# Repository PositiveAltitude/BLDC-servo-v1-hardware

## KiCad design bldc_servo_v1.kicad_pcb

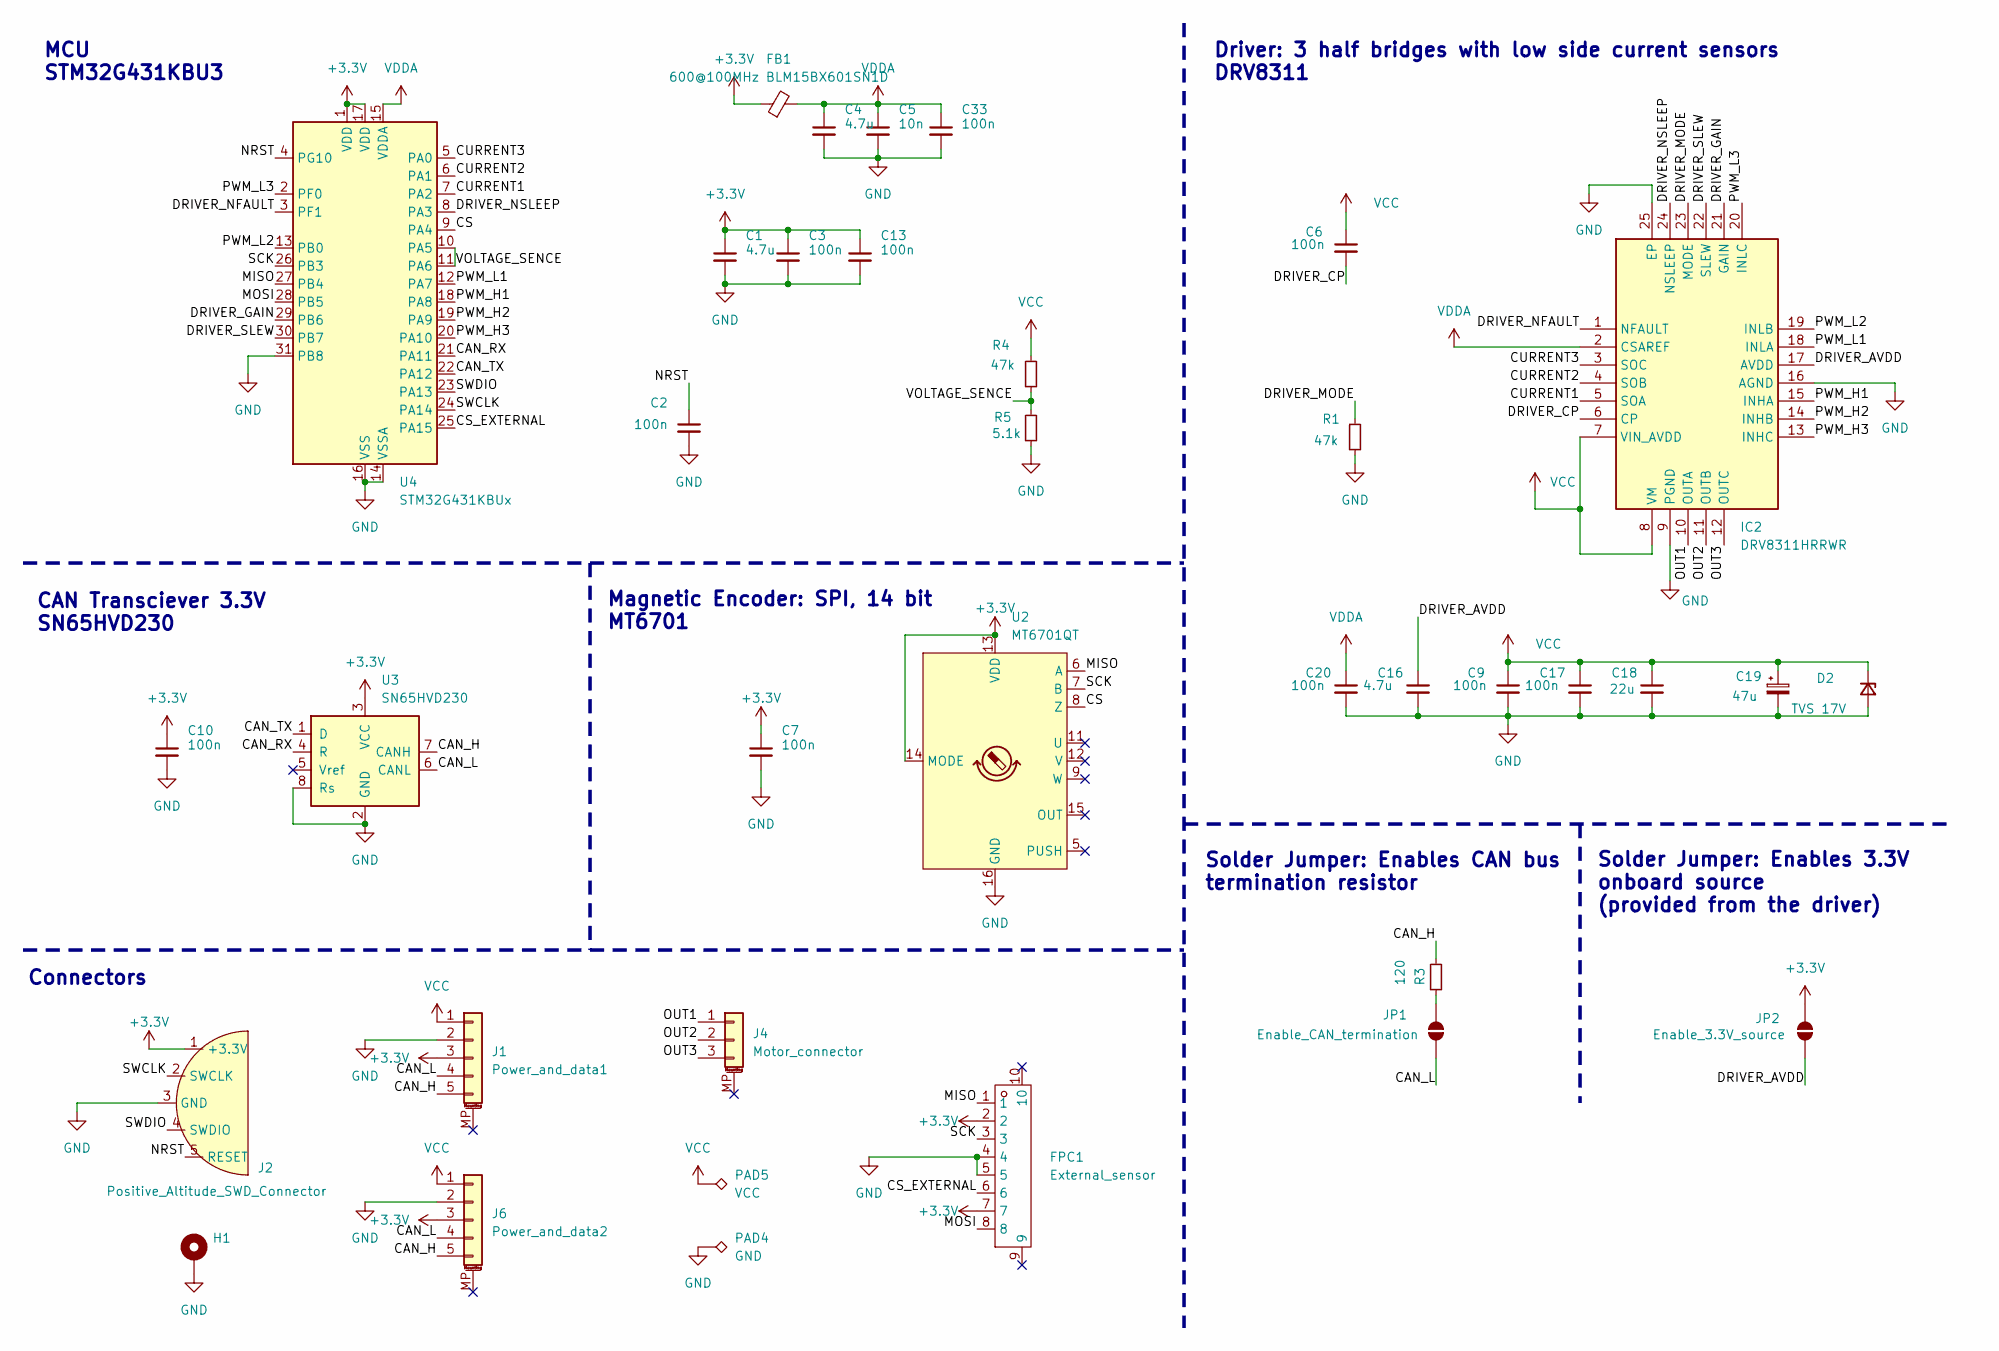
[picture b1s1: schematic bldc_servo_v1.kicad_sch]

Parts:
C1, C4, C16: 4.7u; C_0603_1608Metric_Pad1.08x0.95mm_HandSolder; LCSC C162274
C2, C3, C6, C7, C9, C10, C13, C17, C20, C33: 100n; C_0402_1005Metric_Pad0.74x0.62mm_HandSolder; LCSC C77020
C5: 10n; C_0402_1005Metric_Pad0.74x0.62mm_HandSolder; LCSC C77019
C18: 22u; C_1210_3225Metric_Pad1.33x2.70mm_HandSolder; LCSC C21397
C19: 47u; CP_Elec_6.3x5.8; LCSC C2161781
D2: TVS 17V; D_SOD-123F; LCSC C353303
FB1: 600@100MHz BLM15BX601SN1D; R_0402_1005Metric_Pad0.72x0.64mm_HandSolder; LCSC C710336
FPC1: External_sensor; FPC-SMD_8P-P0.50_HC-FPC-05-09-8RLTAG; Manufacturer Part HC-FPC-05-09-8RLTAG; LCSC Part Name 翻盖式 双侧触点/上下接 P数:8P 间距:0.5mm
H1: MountingHole_Pad; MountingHole_2.2mm_M2_Pad_TopBottom
IC2: DRV8311HRRWR; DRV8311PRRWR; Mouser Part Number 595-DRV8311HRRWR
J1: Power_and_data1; JST_SH_SM05B-SRSS-TB_1x05-1MP_P1.00mm_Horizontal; LCSC C136657
J2: Positive_Altitude_SWD_Connector
J4: Motor_connector; JST_PH_S3B-PH-SM4-TB_1x03-1MP_P2.00mm_Horizontal; LCSC C265101
J6: Power_and_data2; JST_SH_SM05B-SRSS-TB_1x05-1MP_P1.00mm_Horizontal; LCSC C136657
JP1: Enable_CAN_termination; SolderJumper-2_P1.3mm_Open_RoundedPad1.0x1.5mm
JP2: Enable_3.3V_source; SolderJumper-2_P1.3mm_Open_RoundedPad1.0x1.5mm
PAD4: GND; TestPoint_Pad_1.5x1.5mm
PAD5: VCC; TestPoint_Pad_1.5x1.5mm
R1, R4: 47k; R_0402_1005Metric_Pad0.72x0.64mm_HandSolder; LCSC C93943
R3: 120; R_0402_1005Metric_Pad0.72x0.64mm_HandSolder; LCSC C114758
R5: 5.1k; R_0402_1005Metric_Pad0.72x0.64mm_HandSolder; LCSC C105872
U2: MT6701QT; QFN-16-1EP_3x3mm_P0.5mm_EP1.7x1.7mm; LCSC C2913974
U3: SN65HVD230; SOIC-8_3.9x4.9mm_P1.27mm; LCSC C12084
U4: STM32G431KBUx; QFN-32-1EP_5x5mm_P0.5mm_EP3.45x3.45mm; LCSC C1341901

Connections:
+3.3V: C1.1, C3.1, C7.1, C10.1, C13.1, FB1.1, FPC1.2, FPC1.7, J1.3, J2.1 (+3.3V), J6.3, JP2.2 (B), U2.13 (VDD), U2.14 (MODE), U3.3 (VCC), U4.1 (VDD), U4.17 (VDD)
/CAN_H: J1.5, J6.5, R3.2, U3.7 (CANH)
/CAN_L: J1.4, J6.4, JP1.1 (A), U3.6 (CANL)
/CAN_RX: U3.4 (R), U4.21 (PA11)
/CAN_TX: U3.1 (D), U4.22 (PA12)
/CS: U2.8 (Z), U4.9 (PA4)
/CS_EXTERNAL: FPC1.6, U4.25 (PA15)
/CURRENT1: IC2.5 (SOA), U4.7 (PA2)
/CURRENT2: IC2.4 (SOB), U4.6 (PA1)
/CURRENT3: IC2.3 (SOC), U4.5 (PA0)
/DRIVER_AVDD: C16.1, IC2.17 (AVDD), JP2.1 (A)
/DRIVER_CP: C6.2, IC2.6 (CP)
/DRIVER_GAIN: IC2.21 (GAIN), U4.29 (PB6)
/DRIVER_MODE: IC2.23 (MODE), R1.1
/DRIVER_NFAULT: IC2.1 (NFAULT), U4.3 (PF1)
/DRIVER_NSLEEP: IC2.24 (NSLEEP), U4.8 (PA3)
/DRIVER_SLEW: IC2.22 (SLEW), U4.30 (PB7)
/MISO: FPC1.1, U2.6 (A), U4.27 (PB4)
/MOSI: FPC1.8, U4.28 (PB5)
/NRST: C2.1, J2.5 (RESET), U4.4 (PG10)
/OUT1: IC2.10 (OUTA), J4.1
/OUT2: IC2.11 (OUTB), J4.2
/OUT3: IC2.12 (OUTC), J4.3
/PWM_H1: IC2.15 (INHA), U4.18 (PA8)
/PWM_H2: IC2.14 (INHB), U4.19 (PA9)
/PWM_H3: IC2.13 (INHC), U4.20 (PA10)
/PWM_L1: IC2.18 (INLA), U4.12 (PA7)
/PWM_L2: IC2.19 (INLB), U4.13 (PB0)
/PWM_L3: IC2.20 (INLC), U4.2 (PF0)
/SCK: FPC1.3, U2.7 (B), U4.26 (PB3)
/SWCLK: J2.2 (SWCLK), U4.24 (PA14)
/SWDIO: J2.4 (SWDIO), U4.23 (PA13)
/VOLTAGE_SENCE: R4.1, R5.2, U4.10 (PA5), U4.11 (PA6)
GND: C1.2, C2.2, C3.2, C4.2, C5.2, C7.2, C9.2, C10.2, C13.2, C16.2, C17.2, C18.2, C19.2, C20.2, C33.2, D2.2 (A), FPC1.4, FPC1.5, H1.1, IC2.9 (PGND), IC2.16 (AGND), IC2.25 (EP), J1.2, J2.3 (GND), J6.2, PAD4.1, R1.2, R5.1, U2.16 (GND), U2.17 (GND), U3.2 (GND), U3.8 (Rs), U4.14 (VSSA), U4.16 (VSS), U4.31 (PB8), U4.32 (VSS), U4.33 (VSS)
unnamed: JP1.2 (B), R3.1
VCC: C6.1, C9.1, C17.1, C18.1, C19.1, D2.1 (K), IC2.7 (VIN_AVDD), IC2.8 (VM), J1.1, J6.1, PAD5.1, R4.2
VDDA: C4.1, C5.1, C20.1, C33.1, FB1.2, IC2.2 (CSAREF), U4.15 (VDDA)

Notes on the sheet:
MCU STM32G431KBU3
Solder Jumper: Enables 3.3V onboard source (provided from the driver)
Driver: 3 half bridges with low side current sensors DRV8311
Magnetic Encoder: SPI, 14 bit MT6701
CAN Transciever 3.3V SN65HVD230
Solder Jumper: Enables CAN bus termination resistor
Connectors

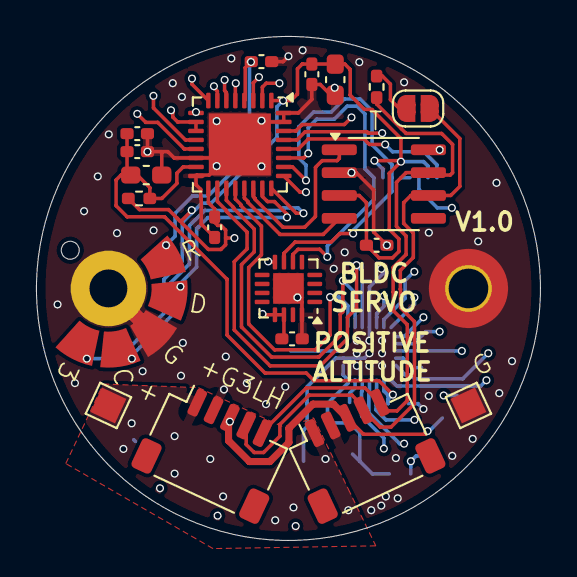
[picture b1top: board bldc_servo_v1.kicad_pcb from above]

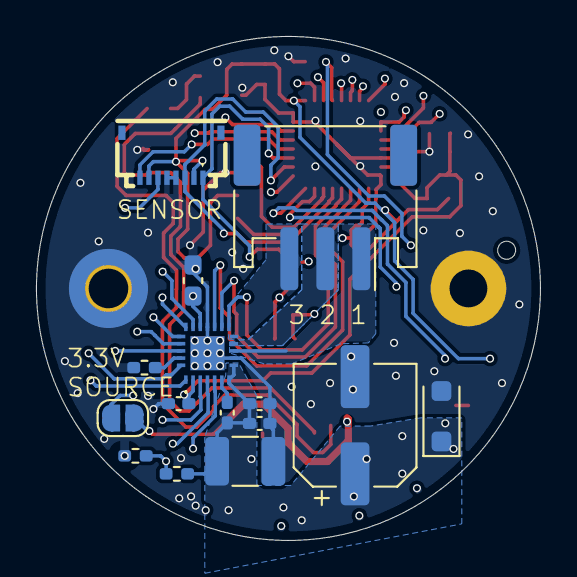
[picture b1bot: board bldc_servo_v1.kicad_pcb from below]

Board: 6 copper layers, 28.0 x 28.0 mm, 36 parts (15 on the bottom side), 37 nets.

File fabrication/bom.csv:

Comment,Designator,Footprint,LCSC
4.7u,"C1,C4,C16",Capacitor_SMD:C_0603_1608Metric_Pad1.08x0.95mm_HandSolder,C162274
100n,"C2,C3,C6,C7,C9,C10,C13,C17,C20,C33",Capacitor_SMD:C_0402_1005Metric_Pad0.74x0.62mm_HandSolder,C77020
TVS 17V,D2,Diode_SMD:D_SOD-123F,C353303
Motor_connector,J4,Connector_JST:JST_PH_S3B-PH-SM4-TB_1x03-1MP_P2.00mm_Horizontal,C265101
SN65HVD230,U3,Package_SO:SOIC-8_3.9x4.9mm_P1.27mm,C12084
DRV8311HRRWR,IC2,DRV8311HRRWR:DRV8311PRRWR,C5218862
120,R3,Resistor_SMD:R_0402_1005Metric_Pad0.72x0.64mm_HandSolder,C114758
22u,C18,Capacitor_SMD:C_1210_3225Metric_Pad1.33x2.70mm_HandSolder,C21397
MT6701QT,U2,Package_DFN_QFN:QFN-16-1EP_3x3mm_P0.5mm_EP1.7x1.7mm,C2913974
External_sensor,FPC1,HCTL HC-FPC-05-09-8RLTAG:FPC-SMD_8P-P0.50_HC-FPC-05-09-8RLTAG,C5213749
47u,C19,Capacitor_SMD:CP_Elec_6.3x5.8,C2161781
47k,"R1,R4",Resistor_SMD:R_0402_1005Metric_Pad0.72x0.64mm_HandSolder,C93943
STM32G431KBUx,U4,Package_DFN_QFN:QFN-32-1EP_5x5mm_P0.5mm_EP3.45x3.45mm,C1341901
Power_and_data1,J1,Connector_JST:JST_SH_SM05B-SRSS-TB_1x05-1MP_P1.00mm_Horizontal,C136657
Power_and_data2,J6,Connector_JST:JST_SH_SM05B-SRSS-TB_1x05-1MP_P1.00mm_Horizontal,C136657
10n,C5,Capacitor_SMD:C_0402_1005Metric_Pad0.74x0.62mm_HandSolder,C77019
600@100MHz BLM15BX601SN1D,FB1,Resistor_SMD:R_0402_1005Metric_Pad0.72x0.64mm_HandSolder,C710336
5.1k,R5,Resistor_SMD:R_0402_1005Metric_Pad0.72x0.64mm_HandSolder,C105872

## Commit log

2025-04-02 6 layer board draft
2025-04-03 Almost finished board and pannel
2025-04-03 panel
2025-04-04 Component IDs and cleanup
2025-04-05 Upgrading to KiCad 9
2025-04-05 Rename project
2025-04-05 Fabrication output
2025-04-05 Tooling and fiducials
2025-04-05 Small fixes
2025-04-05 Adjustments to panel, LCSC bom
